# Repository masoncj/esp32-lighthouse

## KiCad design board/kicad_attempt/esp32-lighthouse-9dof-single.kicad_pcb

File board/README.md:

# ESP-32 Lighthouse Board

Add on board for SparkFun ESP32 Thing that determines absolute position and orientation in spacing using the Lighthouse 
and an IMU.

There will eventually be multiple boards here, but currently only the first exists:

* **[Single-chip TS4231 Board](#esp-32-lighthouse-9dof-single)**, `esp32-lighthouse-9dof-single`: directly uses the newer TS4231 chip.  This uses fine parts (a 1.6mm-square chip)), so it will be harder to solder.  It's substantially cheaper however and uses the newer chip.
* **[Castellated Module](#castellated_module)**, `esp32-lighthouse-proto-mod`: uses the TS3633 prototyping module ([datasheet](https://www.triadsemi.com/wp-content/uploads/dlm_uploads/2016/09/TS3633-CM1_Datasheet-Rev-B.pdf)), for easier soldering, but more expensive.

## Single Chip TS4231 Board

Uses TS4231 WSCLP (read: tiny) chip.  Also includes 9 degree-of-freedom (9DOF) inertia measurement unit (IMU), which contains a 3-axis accelerometer, gyroscope, and magnetometer (compass). With these components it should be able to get absolute position and orientation.

### Components

The [bill of materials](https://docs.google.com/spreadsheets/d/1Z215yCS3Rhd9xmao2OCiXYKUPr7iIdqlMC3hmtdATUM/edit#gid=0) (Google sheets link) includes:

* Lighthouse light-to-digital converter chip, TS4231 ([datasheet](https://www.triadsemi.com/wp-content/uploads/dlm_uploads/2017/06/triad_semi_ts4231_datasheet_rev_a.pdf), [design guidelines](https://www.triadsemi.com/download/18126/))
* BPW34S Photodiode ([datasheet](https://media.digikey.com/pdf/Data%20Sheets/Osram%20PDFs/bpw34_spdf.pdf))
* LSM9 9-axis digital accelerometer, gyroscope, and magnetometer (optional) ([datasheet](http://www.st.com/content/ccc/resource/technical/document/datasheet/1e/3f/2a/d6/25/eb/48/46/DM00103319.pdf/files/DM00103319.pdf/jcr:content/translations/en.DM00103319.pdf))

### Pins

Avoid: 0 (Button), 5 (LED), 34-39 (Input Only, No Pulls)

Use: 13, 12, 14, 27, 26, 25, 16, 17, 14, 2, 15, 18, 23

| Device | ESP32 Peripheral | ESP32 Pin | Notes |
| --- | --- | --- | --- |
| TS4231 D | RMT timer 01 | 25 | |
| TS4231 E | RMT timer 02 | 26 | |
| LSM9 SCL/SPC | GPIO16 | 16 | | 
| LSM9 SDA/SDI/SDO (4) | GPIO17 | 17 | | 
| LSM9 SDO_AG (5) | GPIO4 | 4 | | 
| LSM9 SDO_M (6) | GPIO2 | 2 | |
| LSM9 CS_AG (7) |  GPIO15 | 15 | | 
| LSM9 CS_M (8) | GPIO18 | 18 | | 
| LSM9 DRDY_M (9) | GPIO23 | 23 | 
| LSM9 INT_M (10)  | GPIO27	 | 27 | |
| LSM9 INT1_AG (11) | GPIO14 | 14 | |
| LSM9 INT2_AG (12) | GPIO12 | 12 | |
| LSM9 DEN_AG (13) | GPIO13 | 13 | |

13 pins

### Layout

I first attempted to create the board in [KiCad](http://kicad-pcb.org/).  I thought it would be great to be able to share the design with others who could modify and tweak it.  However after a few intermittent weeks of frustration trying to learn KiCad's poor user interface (using, for instance, [this tutorial](http://babryce.com/kicad/tutorial.html)), I gave up.  The vestiges of that attempt are [here](kicad_attempt).  I got a schematic completed and the footprints designed but I just couldn't get used to KiCad's PCB editor and library management.  The fact that it takes about 10 clicks to update a footprint on a board is just ridiculous.  See [this article](http://diy-scib.org/blog/working-kicads-terrible-library-management) for additional color on some of what I was running into.

I'll come back to KiCad at some point, but I just ran out of time with a hard deadline to produce boards for a class I was giving.

I then moved to my usual PCB layout tool, [DipTrace](https://www.diptrace.com/).  I was able to knock out the components, footprints, schematic, and layout in about a day.

Note, the TS4231 is essentially a very high gain amplifier for a specific carrier frequency.  The [design guidelines](https://www.triadsemi.com/download/18126) are very insistent that it's important to minimize noise and stray capacitance.  We use a crosshatched ground (to minimize capacitance), short/matched traces (to minimize differential noise), and try to follow closely the layout on page 4.  However, I used 0603 caps instead of 0402.  I figured that one extremely fiddly part per board was enough.

Schematic ([PDF](outputs/esp32-lighthouse-9dof-single-v1-schem.pdf)):

Board Layout ([PDF](outputs/esp32-lighthouse-9dof-single-v1-board.pdf)):

[Gerbers](outputs/esp32-lighthouse-9dof-single-v1)

## Castellated Module

This was an earlier attempt at using a prototyping module before I realized how much it would cost.

### Castellated Module Notes

* TS3633 Standby (12) 11 o'clock
* TS3633 VCC (1) 10 o'clock
* TS3633 Envelope  9 o'clock
* TD3633 GND 8 o'clock

Mount CM upside down?

* 0.1" pin spacing
* 0.4" pin row spacing (NOT 0.5" as indicated on datasheet -- footprint is correct)
* Standby pin in 0.1" and up 0.1"

### Using Castellated Prototyping Module vs Building ourselves
Cost analysis

| Component | Price @20|
| --- | --- |
| TS3633-CM1 ([Datasheet](https://www.triadsemi.com/download/16617/)) | $6.95 | 
| **Total** | **$6.95** |

Vs

| Component | Price @20|
| --- | --- |
| TS4231 Light to digital converter ([Datasheet](https://www.triadsemi.com/download/17260/)) | $0.95 | 
| BPW34S Photodiode ([Datasheet](http://www.mouser.com/ds/2/311/BPW%2034%20S,%20Lead%20(Pb)%20Free%20Product%20-%20RoHS%20Compliant-335799.pdf)) | $0.553 |
| Capacitor 1.0 uF 0402 | $0.036 |
| Capacitor 0.1 uF 0402 10% | $0.015 | 
| Resistor 15k 1% | $0.023
| **Total** | **$1.577** |

#### Optional 9DOF Accel/Gyro/Mag

| Component | Price @20|
| --- | --- |
| LSM9DS1 | $5.28 |

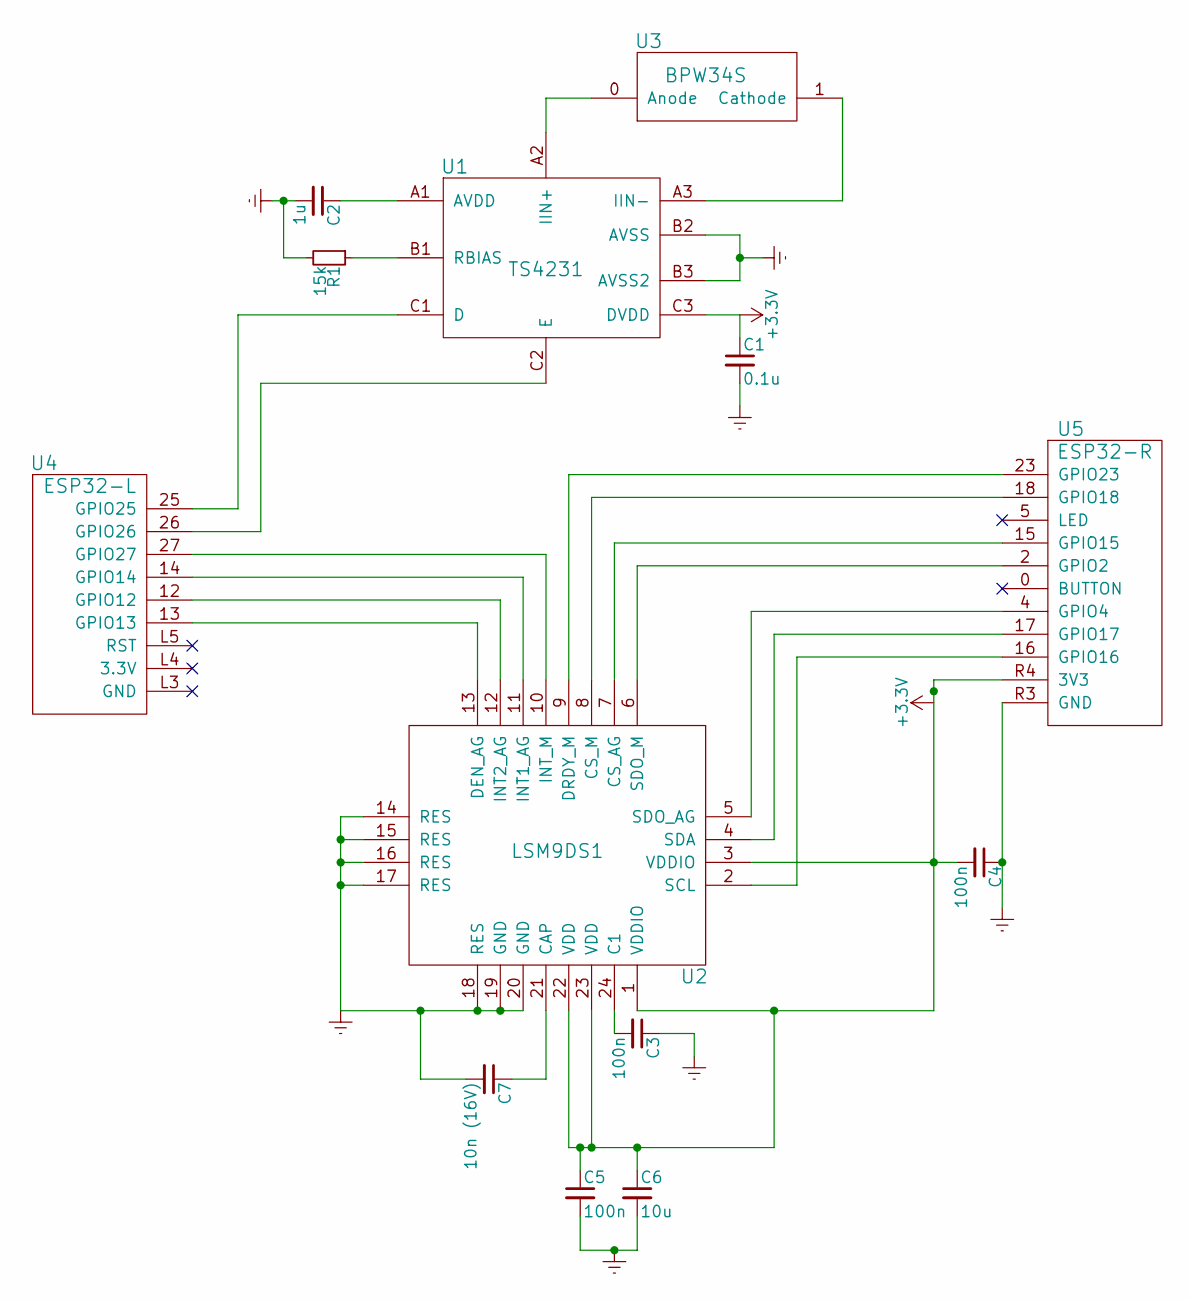
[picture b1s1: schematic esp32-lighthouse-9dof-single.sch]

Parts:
C1: 0.1u; C_0603
C2: 1u; C_0603
C3, C4, C5: 100n; C_0603
C6: 10u; C_0603
C7: 10n (16V); C_0603
R1: 15k; R_0603
U1: TS4231
U2: LSM9DS1
U3: BPW34S
U4: ESP32-L
U5: ESP32-R

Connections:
Earth: C1.2, C2.2, C3.1, C4.1, C5.2, C6.2, C7.2, R1.2, U1.B2 (AVSS), U1.B3 (AVSS2), U2.14 (RES), U2.15 (RES), U2.16 (RES), U2.17 (RES), U2.18 (RES), U2.19 (GND), U2.20 (GND), U5.R3 (GND)
unnamed: C2.1, U1.A1 (AVDD)
unnamed: C3.2, U2.24 (C1)
unnamed: C7.1, U2.21 (CAP)
unnamed: R1.1, U1.B1 (RBIAS)
unnamed: U1.A2 (IIN+), U3.0 (Anode)
unnamed: U1.A3 (IIN-), U3.1 (Cathode)
unnamed: U1.C1 (D), U4.25 (GPIO25)
unnamed: U1.C2 (E), U4.26 (GPIO26)
unnamed: U2.2 (SCL), U5.16 (GPIO16)
unnamed: U2.4 (SDA), U5.17 (GPIO17)
unnamed: U2.5 (SDO_AG), U5.4 (GPIO4)
unnamed: U2.6 (SDO_M), U5.2 (GPIO2)
unnamed: U2.7 (CS_AG), U5.15 (GPIO15)
unnamed: U2.8 (CS_M), U5.18 (GPIO18)
unnamed: U2.9 (DRDY_M), U5.23 (GPIO23)
unnamed: U2.10 (INT_M), U4.27 (GPIO27)
unnamed: U2.11 (INT1_AG), U4.14 (GPIO14)
unnamed: U2.12 (INT2_AG), U4.12 (GPIO12)
unnamed: U2.13 (DEN_AG), U4.13 (GPIO13)

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
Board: 2 copper layers, 13 parts (0 on the bottom side), 22 nets, no tracks yet.

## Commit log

2017-12-29 Initial esp32-lighthouse-9dof-single board
2017-12-29 Fix image sizes in README.
2017-12-29 Fix links in README.
